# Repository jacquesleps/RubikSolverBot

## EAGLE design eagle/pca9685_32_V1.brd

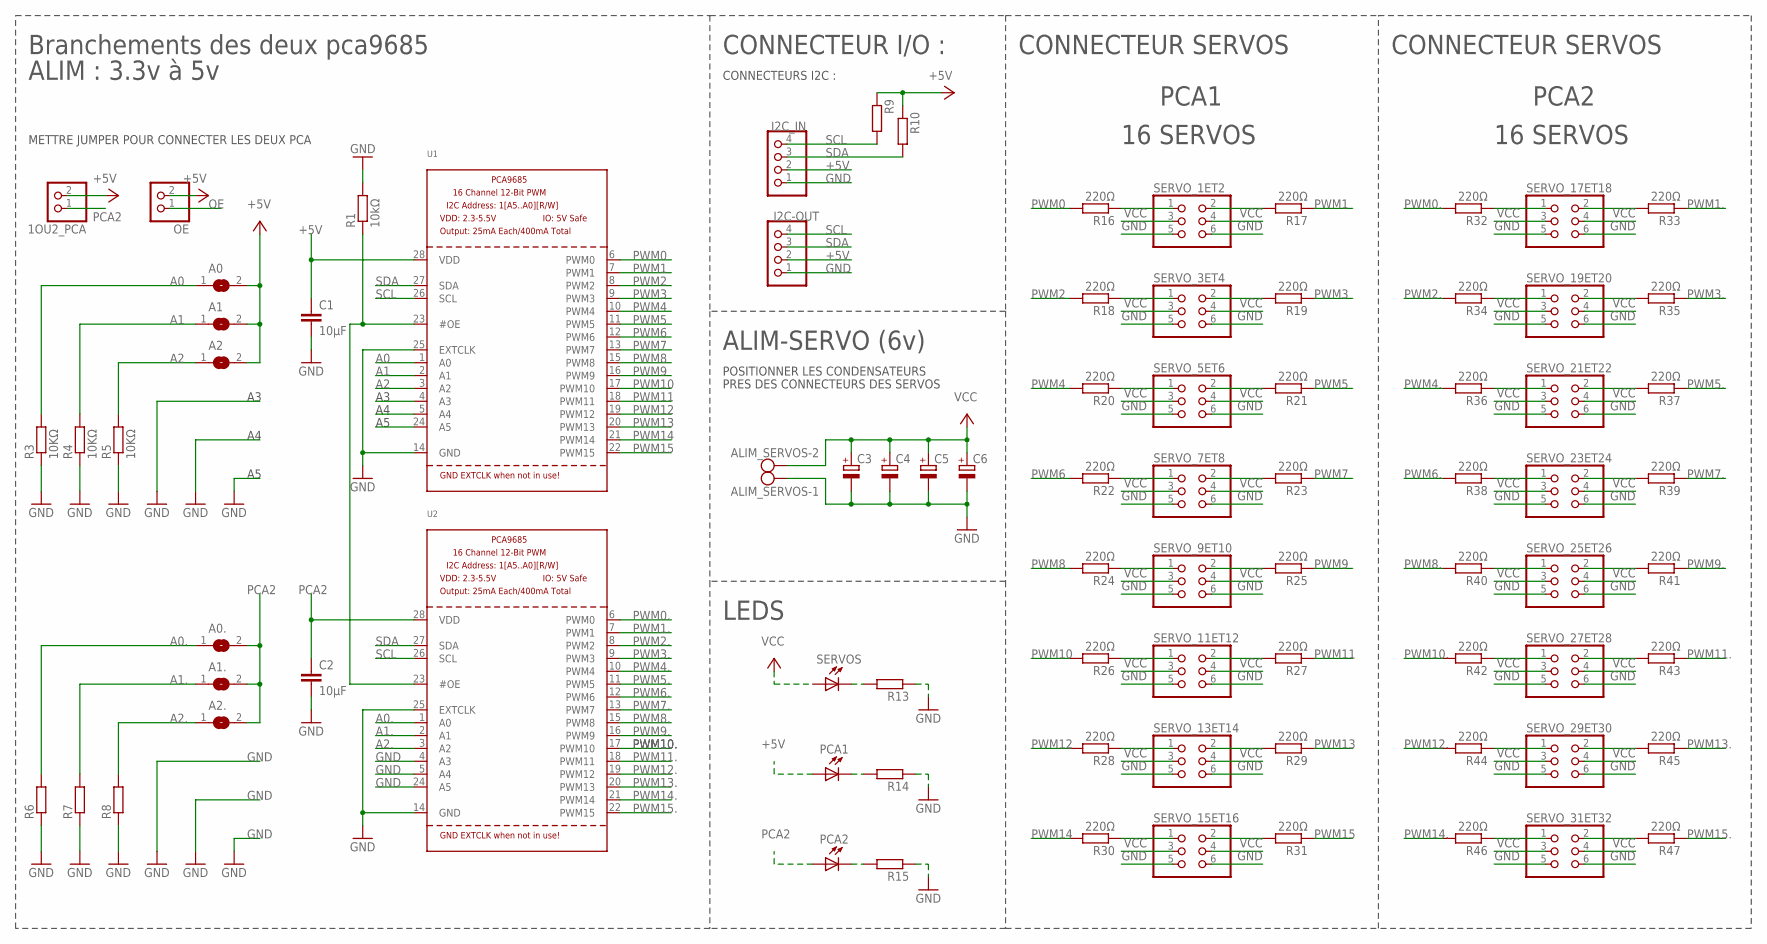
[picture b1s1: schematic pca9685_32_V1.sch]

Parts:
1OU2_PCA: PINHD-1X2; 1X02
A0, A0., A1, A1., A2, A2.: SOLDERJUMPERREFLOW_NOPASTE; SOLDERJUMPER_REFLOW_NOPASTE
ALIM_SERVOS: AK500/2
C1, C2: 10µF; C0805
C3, C4, C5, C6: CPOL-EUE3.5-10; E3,5-10
I2C-OUT, I2C_IN: PINHD-1X4; 1X04
OE: PINHD-1X2; 1X02
PCA1, PCA2: LEDCHIP-LED0805; CHIP-LED0805
R1: 10kΩ; R0805
R3, R4, R5: 10KΩ; R1206
R6, R7, R8: R-EU_R1206; R1206
R9, R10, R13, R14, R15: R-EU_R0805; R0805
R16, R17, R18, R19, R20, R21, R22, R23, R24, R25, R26, R27, R28, R29, R30, R31, R32, R33, R34, R35, R36, R37, R38, R39, R40, R41, R42, R43, R44, R45, R46, R47: 220Ω; R0805
SERVOS: LEDCHIP-LED0805; CHIP-LED0805
SERVO_1ET2, SERVO_3ET4, SERVO_5ET6, SERVO_7ET8, SERVO_9ET10, SERVO_11ET12, SERVO_13ET14, SERVO_15ET16, SERVO_17ET18, SERVO_19ET20, SERVO_21ET22, SERVO_23ET24, SERVO_25ET26, SERVO_27ET28, SERVO_29ET30, SERVO_31ET32: PINHD-2X3; 2X03
U1, U2: PCA9685; TSSOP28

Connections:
+5V: 1OU2_PCA.2, A0.2, A1.2, A2.2, C1.1, I2C-OUT.2, I2C_IN.2, OE.2, PCA1.A, R9.1, R10.1, U1.28 (VDD)
A0: A0.1, R3.2, U1.1 (A0)
A0.: A0..1, R6.2, U2.1 (A0)
A1: A1.1, R4.2, U1.2 (A1)
A1.: A1..1, R7.2, U2.2 (A1)
A2: A2.1, R5.2, U1.3 (A2)
A2.: A2..1, R8.2, U2.3 (A2)
GND: ALIM_SERVOS.1, C1.2, C2.2, C3.-, C4.-, C5.-, C6.-, I2C-OUT.1, I2C_IN.1, R1.2, R3.1, R4.1, R5.1, R6.1, R7.1, R8.1, R13.1, R14.1, R15.1, U1.4 (A3), U1.5 (A4), U1.14 (GND), U1.24 (A5), U1.25 (EXTCLK), U2.4 (A3), U2.5 (A4), U2.14 (GND), U2.24 (A5), U2.25 (EXTCLK)
unnamed: R13.2, SERVOS.C
unnamed: PCA1.C, R14.2
unnamed: PCA2.C, R15.2
unnamed: R18.1, SERVO_3ET4.1
unnamed: R19.2, SERVO_3ET4.2
unnamed: R22.1, SERVO_7ET8.1
unnamed: R23.2, SERVO_7ET8.2
unnamed: R16.1, SERVO_1ET2.1
unnamed: R17.2, SERVO_1ET2.2
unnamed: R21.2, SERVO_5ET6.2
unnamed: R20.1, SERVO_5ET6.1
unnamed: R24.1, SERVO_9ET10.1
unnamed: R25.2, SERVO_9ET10.2
unnamed: R27.2, SERVO_11ET12.2
unnamed: R26.1, SERVO_11ET12.1
unnamed: R28.1, SERVO_13ET14.1
unnamed: R29.2, SERVO_13ET14.2
unnamed: R30.1, SERVO_15ET16.1
unnamed: R31.2, SERVO_15ET16.2
unnamed: R32.1, SERVO_17ET18.1
unnamed: R34.1, SERVO_19ET20.1
unnamed: R36.1, SERVO_21ET22.1
unnamed: R38.1, SERVO_23ET24.1
unnamed: R39.2, SERVO_23ET24.2
unnamed: R37.2, SERVO_21ET22.2
unnamed: R35.2, SERVO_19ET20.2
unnamed: R33.2, SERVO_17ET18.2
unnamed: R46.1, SERVO_31ET32.1
unnamed: R47.2, SERVO_31ET32.2
unnamed: R45.2, SERVO_29ET30.2
unnamed: R44.1, SERVO_29ET30.1
unnamed: R43.2, SERVO_27ET28.2
unnamed: R42.1, SERVO_27ET28.1
unnamed: R40.1, SERVO_25ET26.1
unnamed: R41.2, SERVO_25ET26.2
OE: OE.1, R1.1, U1.23 (#OE), U2.23 (#OE)
PCA2: 1OU2_PCA.1, A0..2, A1..2, A2..2, C2.1, PCA2.A, U2.28 (VDD)
PWM0: R16.2, U1.6 (PWM0)
PWM0.: R32.2, U2.6 (PWM0)
PWM1: R17.1, U1.7 (PWM1)
PWM1.: R33.1, U2.7 (PWM1)
PWM2: R18.2, U1.8 (PWM2)
PWM2.: R34.2, U2.8 (PWM2)
PWM3: R19.1, U1.9 (PWM3)
PWM3.: R35.1, U2.9 (PWM3)
PWM4: R20.2, U1.10 (PWM4)
PWM4.: R36.2, U2.10 (PWM4)
PWM5: R21.1, U1.11 (PWM5)
PWM5.: R37.1, U2.11 (PWM5)
PWM6: R22.2, U1.12 (PWM6)
PWM6.: R38.2, U2.12 (PWM6)
PWM7: R23.1, U1.13 (PWM7)
PWM7.: R39.1, U2.13 (PWM7)
PWM8: R24.2, U1.15 (PWM8)
PWM8.: R40.2, U2.15 (PWM8)
PWM9: R25.1, U1.16 (PWM9)
PWM9.: R41.1, U2.16 (PWM9)
PWM10: R26.2, U1.17 (PWM10)
PWM10.: R42.2, U2.17 (PWM10)
PWM11: R27.1, U1.18 (PWM11)
PWM11.: R43.1, U2.18 (PWM11)
PWM12: R28.2, U1.19 (PWM12)
PWM12.: R44.2, U2.19 (PWM12)
PWM13: R29.1, U1.20 (PWM13)
PWM13.: R45.1, U2.20 (PWM13)
PWM14: R30.2, U1.21 (PWM14)
PWM14.: R46.2, U2.21 (PWM14)
PWM15: R31.1, U1.22 (PWM15)
PWM15.: R47.1, U2.22 (PWM15)
SCL: I2C-OUT.4, I2C_IN.4, R9.2, U1.26 (SCL), U2.26 (SCL)
SDA: I2C-OUT.3, I2C_IN.3, R10.2, U1.27 (SDA), U2.27 (SDA)
VCC: ALIM_SERVOS.2, C3.+, C4.+, C5.+, C6.+, SERVOS.A

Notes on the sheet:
Branchements des deux pca9685
ALIM : 3.3v à 5v
CONNECTEUR I/O :
CONNECTEURS I2C :
ALIM-SERVO (6v)
POSITIONNER LES CONDENSATEURS
PRES DES CONNECTEURS DES SERVOS
CONNECTEUR SERVOS
CONNECTEUR SERVOS
PCA1
PCA2
16 SERVOS
METTRE JUMPER POUR CONNECTER LES DEUX PCA
LEDS

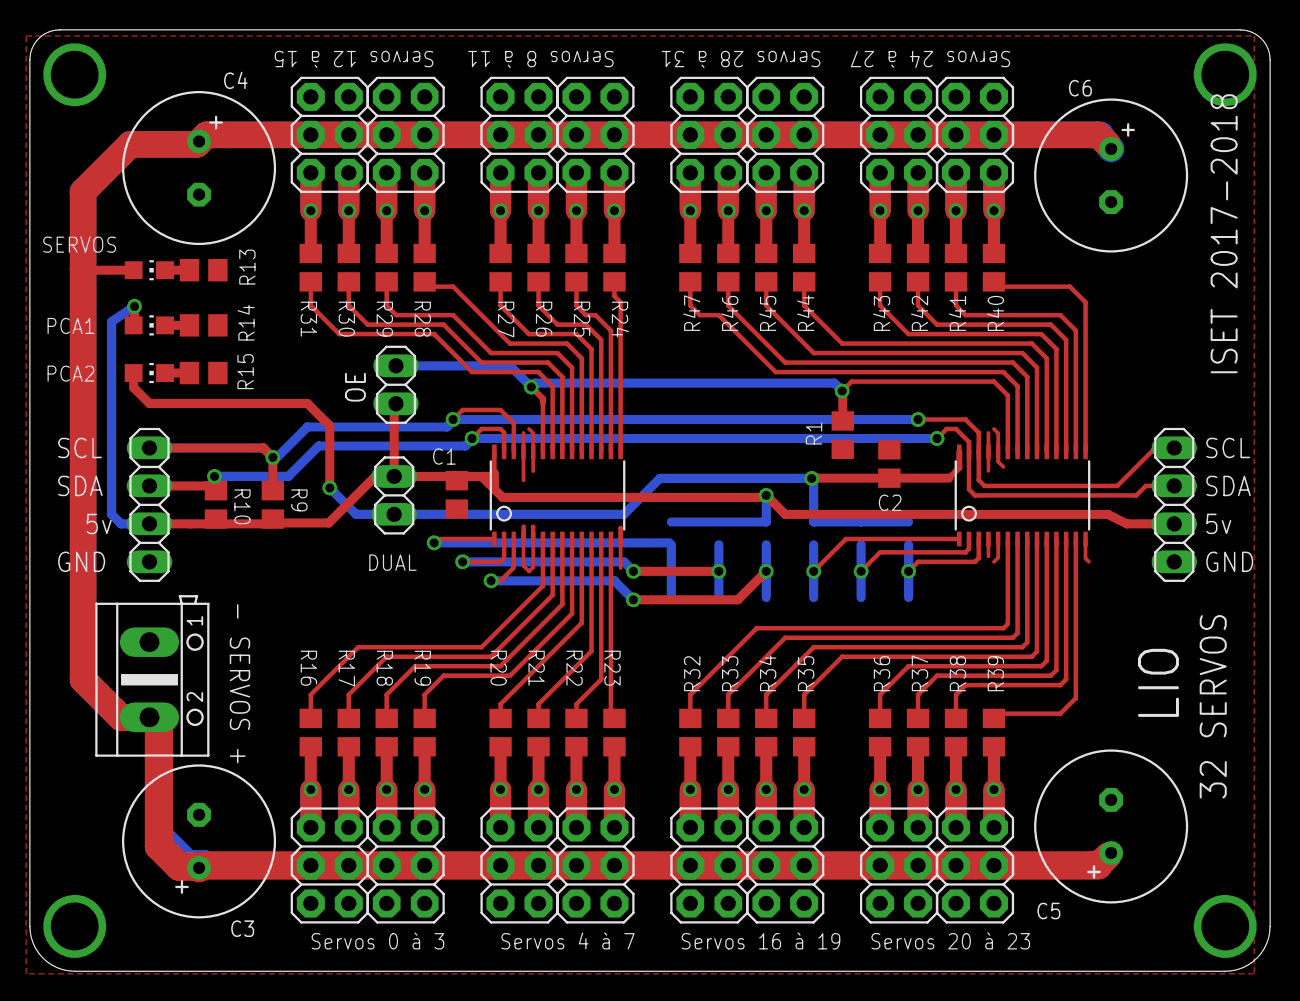
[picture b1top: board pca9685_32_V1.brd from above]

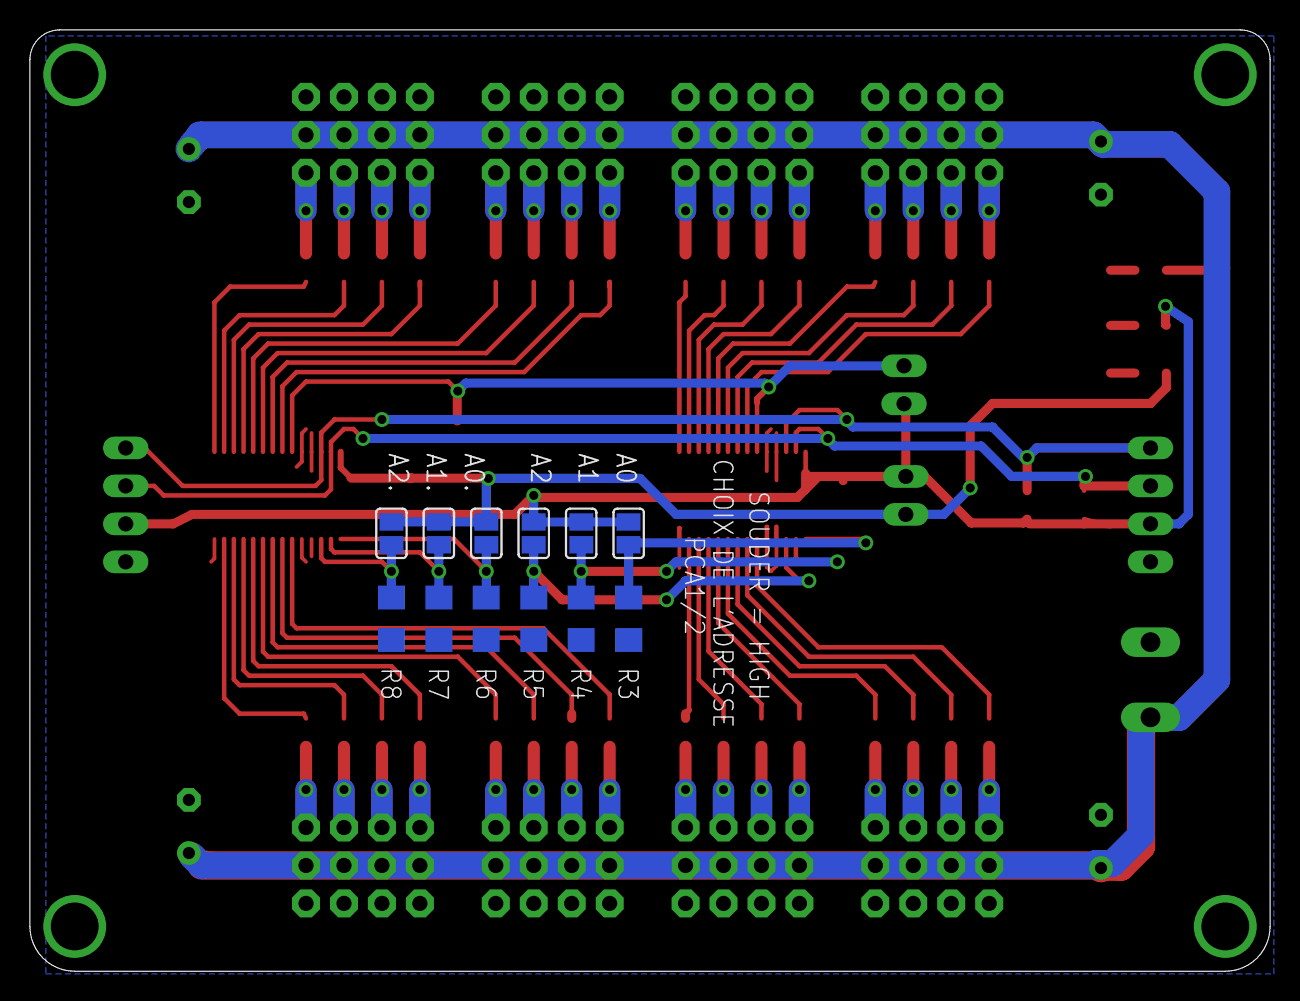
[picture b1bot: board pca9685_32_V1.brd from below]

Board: 2 copper layers, 83.0 x 63.0 mm, 82 parts (12 on the bottom side), 80 nets.

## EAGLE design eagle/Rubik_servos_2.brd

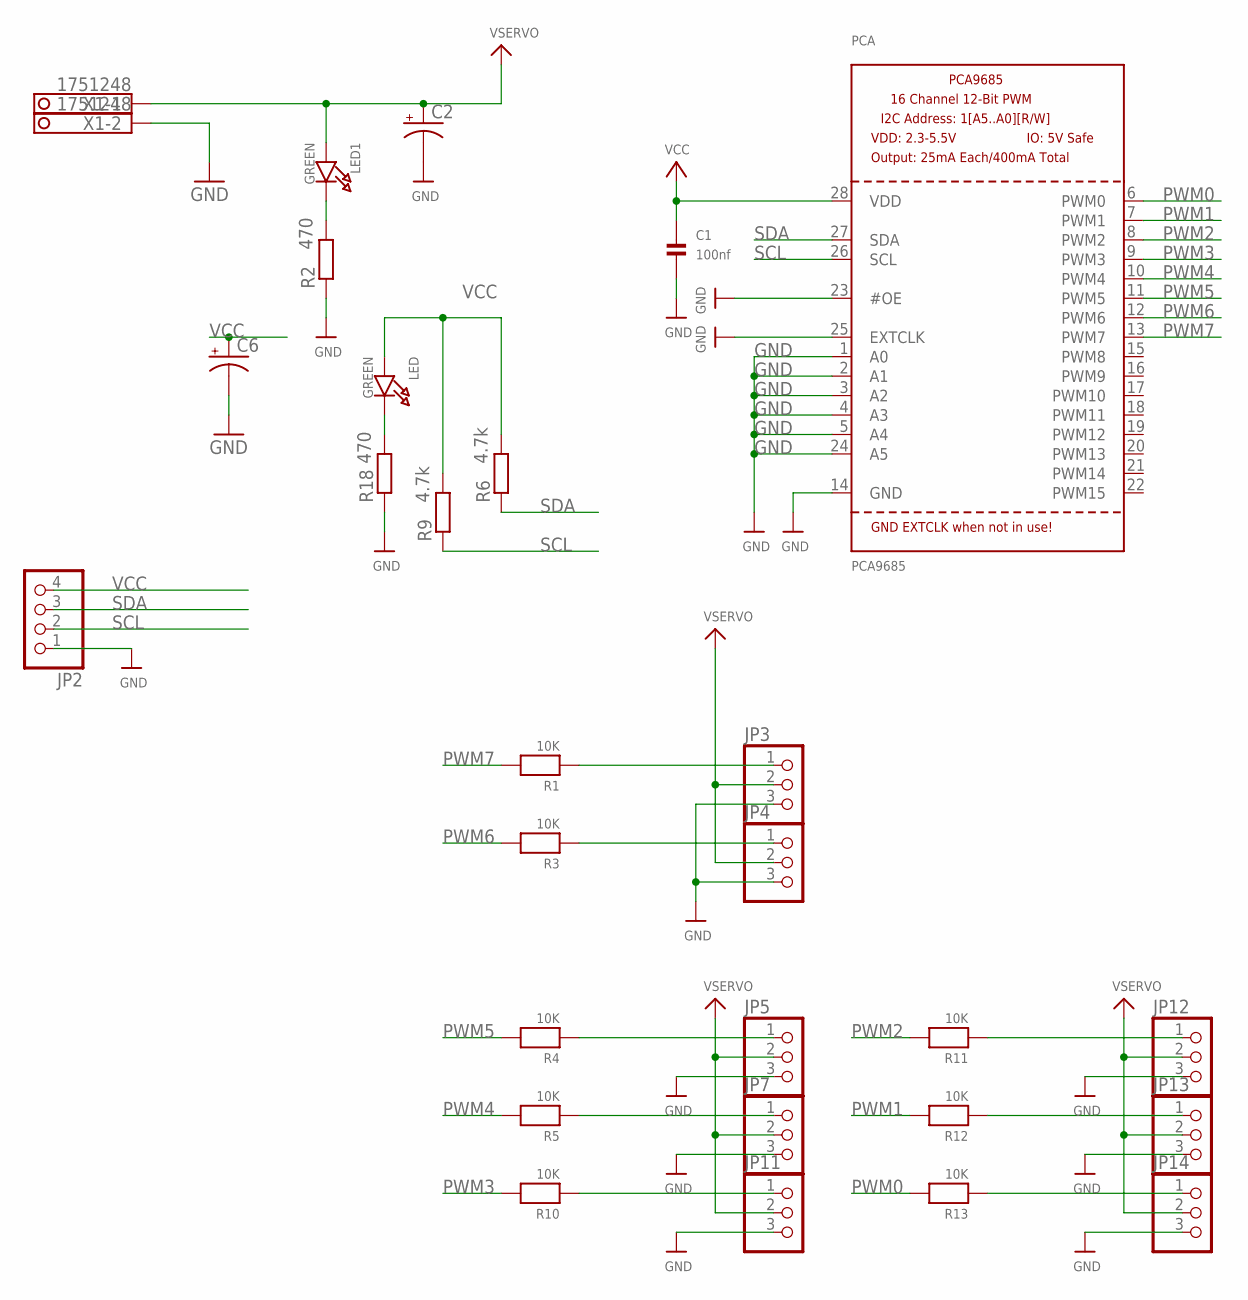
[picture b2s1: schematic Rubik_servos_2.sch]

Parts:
C1: 100nf; 0805
C2: CPOL-USE3.5-8; E3,5-8
C6: CAP_POL3528; EIA3528
JP2: PINHD-1X4"; 1X04
JP3, JP4, JP5, JP7, JP11, JP12, JP13, JP14: PINHD-1X3CB; 1X03-CLEANBIG
LED, LED1: GREEN; CHIPLED_0805
PCA: PCA9685; TSSOP28
R1, R3, R4, R5, R10, R11, R12, R13: 10K; 0603
R2, R18: 470; R0805
R6, R9: 4.7k; R0603
X1: 1751248

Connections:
GND: C1.2, C2.-, C6.C (-), JP2.1, JP3.3, JP4.3, JP5.3, JP7.3, JP11.3, JP12.3, JP13.3, JP14.3, PCA.1 (A0), PCA.2 (A1), PCA.3 (A2), PCA.4 (A3), PCA.5 (A4), PCA.14 (GND), PCA.23 (#OE), PCA.24 (A5), PCA.25 (EXTCLK), R2.1, R18.1, X1.2
unnamed: JP3.1, R1.1
unnamed: JP4.1, R3.1
unnamed: LED1.C, R2.2
unnamed: JP5.1, R4.1
unnamed: JP7.1, R5.1
unnamed: JP11.1, R10.1
unnamed: JP12.1, R11.1
unnamed: JP13.1, R12.1
unnamed: JP14.1, R13.1
unnamed: LED.C, R18.2
PWM0: PCA.6 (PWM0), R13.2
PWM1: PCA.7 (PWM1), R12.2
PWM2: PCA.8 (PWM2), R11.2
PWM3: PCA.9 (PWM3), R10.2
PWM4: PCA.10 (PWM4), R5.2
PWM5: PCA.11 (PWM5), R4.2
PWM6: PCA.12 (PWM6), R3.2
PWM7: PCA.13 (PWM7), R1.2
SCL: JP2.2, PCA.26 (SCL), R9.1
SDA: JP2.3, PCA.27 (SDA), R6.1
VCC: C1.1, C6.A (+), JP2.4, LED.A, PCA.28 (VDD), R6.2, R9.2
VSERVO: C2.+, JP3.2, JP4.2, JP5.2, JP7.2, JP11.2, JP12.2, JP13.2, JP14.2, LED1.A, X1.1

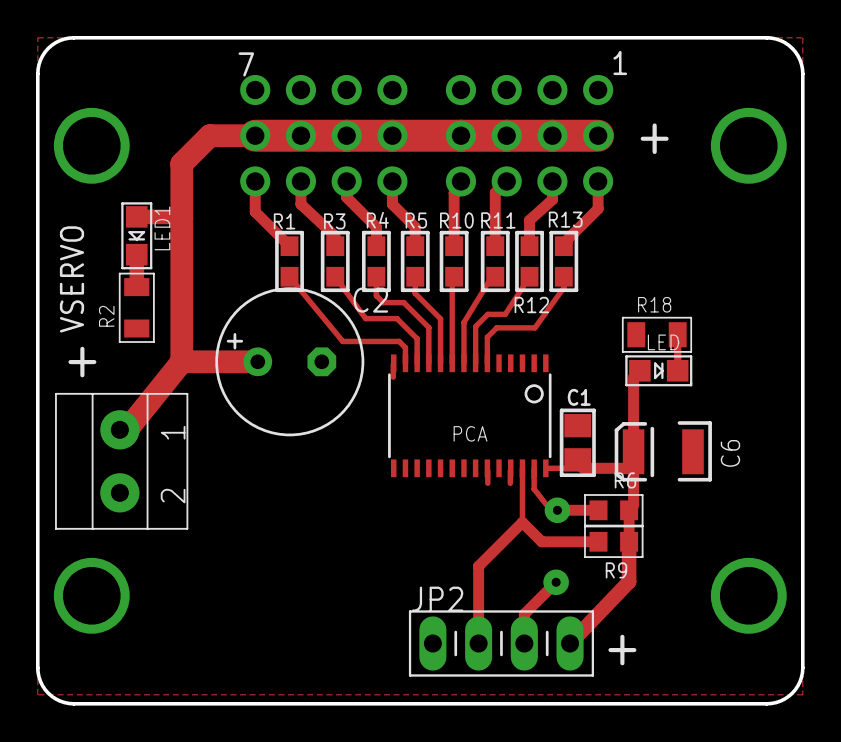
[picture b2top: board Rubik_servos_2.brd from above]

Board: 2 copper layers, 42.5 x 37.0 mm, 28 parts (0 on the bottom side), 23 nets.

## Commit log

2017-11-23 Create vide
2017-11-23 Rename Rubik_servos_2.brd to eagle/Rubik_servos_2.brd
2017-11-23 Rename Rubik_servos_2.sch to eagle/Rubik_servos_2.sch
2017-12-18 Add files via upload
    Programmes de test de la carte ARDUINO MATT.
    CPU ATMEGA32U4, + OLED + SD + NEOPIXEL

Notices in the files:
parts and their libraries:
SparkFun: Licensing: CC v3.0 Share-Alike You are welcome to use this library for commercial purposes.
SparkFun-Retired: Licensing: Creative Commons ShareAlike 4.0 International - https://creativecommons.org/licenses/by-sa/4.0
